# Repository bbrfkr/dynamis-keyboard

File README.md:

# dynamis
"dynamis" is the open-source 65% keyboard integrated with trackball.

## concept
- upgradable
    - This keyboard can be upgraded from sandwitch mounted case to gasket mounted case.
- input only with this 
    - This keyboard is integrated with 34mm trackball, so you need only this to input!
- compact and major
    - 65% layout that is compact and major have been adopted.
- rich layout options
    - split backspace, split left and right shift, split space and iso enter are supported.

## supported key layout

## how to build
### Collect Parts
1. Order semi-assembled pcb by following the [gerbers](https://github.com/bbrfkr/dynamis-keyboard/tree/main/gerbers), [bom](https://github.com/bbrfkr/dynamis-keyboard/blob/main/bom.csv) and [positions](https://github.com/bbrfkr/dynamis-keyboard/blob/main/dynamis-pos.csv) files.
1. Order fr4 plate by following the [plate gerbers](https://github.com/bbrfkr/dynamis-keyboard/tree/main/plate/gerbers).
1. Order the 3d print for trackball cup by the following [stl file](https://github.com/bbrfkr/dynamis-keyboard/blob/main/trackball-cup/trackball-cup.stl) (Here, FDM print should be selected).
1. Choose case options between [sandwitch](https://github.com/bbrfkr/dynamis-keyboard/tree/main/case/sandwitch) and [3d printed](https://github.com/bbrfkr/dynamis-keyboard/tree/main/case/3dp).
1. Collect parts by following the [pcba BOM.md](https://github.com/bbrfkr/dynamis-keyboard/blob/main/BOM.md) and the each BOM.md of selected case option.

### Assemble
1. Assemble semi-assembled pcb completely by following the [pcba build guide](https://github.com/bbrfkr/dynamis-keyboard/blob/main/BUILD.md)
1. Assemble case by following the each BUILD.md of selected case option.

## flash firmware
"dynamis" supports [qmk](https://github.com/qmk/qmk_firmware/tree/master/keyboards/bbrfkr/dynamis). Therefore, you can flash firmware by using [qmk toolbox](https://github.com/qmk/qmk_toolbox).

You can download the firmware for this keyboard from [here](https://github.com/bbrfkr/dynamis-keyboard/releases).

## remap keymap
"dynamis" supports [via](https://www.caniusevia.com/). Therefore, it is recommended that you remap keymap through via. You can download the via definition from [here](https://github.com/bbrfkr/dynamis-keyboard/releases). However, w.r.t. dynamis v2, `KC_F18` and `KC_F19` is hard-coded with `increase DPI` and `decrease DPI` features.

Moreover, "dynamis" is registered in [remap](https://remap-keys.app/catalog/stOy3bAlBUlsGzHCaDIQ). From this, you can remap keymap through web browser.

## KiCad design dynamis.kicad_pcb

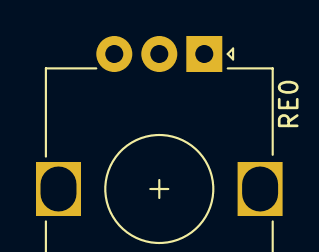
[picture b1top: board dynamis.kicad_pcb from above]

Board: 2 copper layers, 77 parts (0 on the bottom side), 13 nets, no tracks yet.

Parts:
RE0: RotaryEncoder; RotaryEncoder_Alps_EC12E_Vertical_H20mm
SW00_00, SW00_01, SW00_02, SW00_03, SW00_04, SW00_05, SW00_06, SW01_01, SW01_02, SW01_03, SW01_04, SW01_05, SW01_06, SW02_01, SW02_02, SW02_03, SW02_04, SW02_05, SW02_06, SW03_02, SW03_03, SW03_04, SW03_05, SW03_06, SW05_01, SW05_02, SW05_03, SW05_04, SW05_05, SW05_06, SW06_00, SW06_01, SW06_02, SW06_03, SW06_04, SW06_05, SW06_06, SW07_01, SW07_02, SW07_03, SW07_04, SW07_05, SW07_06, SW08_00, SW08_02, SW08_03, SW08_04, SW08_05, SW08_06, SW09_00, SW09_01, SW09_02, SW09_03, SW09_04: SW_Push; MXOnly-1U-Hotswap
SW01_00: SW_Push; MXOnly-1.5U-Hotswap
SW03_00, SW04_00, SW04_01, SW04_02, SW04_06, SW09_05, SW09_06: SW_Push; MXOnly-1.25U-Hotswap
SW04_03: SW_Push; MXOnly-2.25U-Hotswap-ReversedStabilizers
SW04_05: SW_Push; MXOnly-2.75U-Hotswap-ReversedStabilizers
SWBS_L00: SW_Push; MXOnly-2U-Hotswap
SWBS_S00: SW_Push; MXOnly-1U-Hotswap
SWCL_N00: SW_Push; MXOnly-1.75U-Hotswap
SWCL_S00: SW_Push; MXOnly-1U-Hotswap
SWET_AN00: SW_Push; MXOnly-1U-Hotswap
SWET_IS00: SW_Push; MXOnly-2U-Hotswap-ReversedStabilizers
SWLS_L01: SW_Push; MXOnly-2.25U-Hotswap
SWLS_S01: SW_Push; MXOnly-1U-Hotswap
SWRS_L01: SW_Push; MXOnly-2.75U-Hotswap
SWRS_S01: SW_Push; MXOnly-1.75U-Hotswap
SWSP_L04: SW_Push; MXOnly-6.25U-Hotswap
SWSP_S04: SW_Push; MXOnly-1.25U-Hotswap

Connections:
unnamed: SWCL_N00.2, SWCL_S00.2
unnamed: SWLS_L01.2, SWLS_S01.2
unnamed: SWSP_L04.2, SWSP_S04.2
unnamed: SWBS_L00.2, SWBS_S00.2
unnamed: SWET_AN00.2, SWET_IS00.2
unnamed: SWRS_L01.2, SWRS_S01.2
col00: SW00_00.1, SW01_00.1, SW03_00.1, SW04_00.1, SW06_00.1, SW08_00.1, SW09_00.1, SWBS_L00.1, SWBS_S00.1, SWCL_N00.1, SWCL_S00.1, SWET_AN00.1, SWET_IS00.1
col01: SW00_01.1, SW01_01.1, SW02_01.1, SW04_01.1, SW05_01.1, SW06_01.1, SW07_01.1, SW09_01.1, SWLS_L01.1, SWLS_S01.1, SWRS_L01.1, SWRS_S01.1
col02: SW00_02.1, SW01_02.1, SW02_02.1, SW03_02.1, SW04_02.1, SW05_02.1, SW06_02.1, SW07_02.1, SW08_02.1, SW09_02.1
col03: SW00_03.1, SW01_03.1, SW02_03.1, SW03_03.1, SW04_03.1, SW05_03.1, SW06_03.1, SW07_03.1, SW08_03.1, SW09_03.1
col04: SW00_04.1, SW01_04.1, SW02_04.1, SW03_04.1, SW05_04.1, SW06_04.1, SW07_04.1, SW08_04.1, SW09_04.1, SWSP_L04.1, SWSP_S04.1
col05: SW00_05.1, SW01_05.1, SW02_05.1, SW03_05.1, SW04_05.1, SW05_05.1, SW06_05.1, SW07_05.1, SW08_05.1, SW09_05.1
col06: SW00_06.1, SW01_06.1, SW02_06.1, SW03_06.1, SW04_06.1, SW05_06.1, SW06_06.1, SW07_06.1, SW08_06.1, SW09_06.1

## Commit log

2022-06-02 initial
2022-06-11 debug svg
2022-06-12 gasket mount case
2022-06-12 remove unneeded data
2022-06-12 mod bottom case for skrew hole
2022-06-19 mod name of 3dp gasket mount case dir
2022-06-19 mod .gitignore
2022-06-26 impl pcb
2022-06-27 add foam sheet graphics
2022-07-09 acrylic case
2022-07-09 add acrylic case model
2022-07-09 initial as features (#1)
    機能として完成した最初のコミット
2022-07-14 add logo
2022-07-14 move gerbers and add bom template
2022-07-14 update imgur link
2022-07-14 update imgur links
2022-07-14 mod readme
2022-07-14 mod typo
2022-07-14 mod capital letter
2022-07-14 mod bom
2022-07-15 mod boms of cases
2022-07-15 mod boms of cases and readme
2022-07-15 mod readmes
2022-07-15 apply license
2022-07-15 add build.md
2022-07-15 add each dynamis images
2022-07-15 mod to use images branch's images
2022-07-15 mod build guide
2022-07-15 add supported layout image
2022-07-15 add trailing dot
2022-07-15 add build guide and readme for trackball cup
2022-07-15 mod title
2022-07-15 mod stabilizer type
2022-07-15 mod build
2022-07-15 Add docs and logos (#2)
2022-07-15 fix miss link
2022-07-15 fix miss link (#3)
2022-07-16 add ja docs
2022-07-16 move master to main
2022-07-16 Docs ja (#4)
2022-07-16 mod miss link
2022-07-16 mod miss link (#5)
2022-07-16 mod ja -> jp
2022-07-16 mod ja -> jp (#6)
2022-07-16 mod miss link (#7)
2022-07-16 mod the thickness of gasket mount weight
2022-07-16 mod the thickness of gasket mount weight (#8)
2022-07-17 Revert "mod the thickness of gasket mount weight (#8)"
    This reverts commit 7079f59b7b411e1b7f8ee4e9c4865372847dab10.
2022-07-17 Revert "mod the thickness of gasket mount weight (#8)" (#9)
    This reverts commit 7079f59b7b411e1b7f8ee4e9c4865372847dab10.
2022-07-17 mod-bottom-case-stl
2022-07-17 mod-bottom-case-stl (#10)
2022-07-17 Revert "mod-bottom-case-stl (#10)"
    This reverts commit dcce82f15c9197485225979a70152f3f4f279621.
2022-07-17 Revert "mod-bottom-case-stl (#10)" (#11)
    This reverts commit dcce82f15c9197485225979a70152f3f4f279621.
2022-07-17 Revert "Revert "mod the thickness of gasket mount weight (#8)" (#9)"
    This reverts commit 5a923a44f460f610c11262448c813ee0f7480208.
2022-07-17 Revert "Revert "mod the thickness of gasket mount weight (#8)" (#9)" (#12)
    This reverts commit 5a923a44f460f610c11262448c813ee0f7480208.
2022-07-17 mod bom of 3dp
2022-07-17 mod readme of kit
2022-07-17 mod sandwitch build guide
2022-07-17 add images
2022-07-17 add dosc
2022-07-17 mod docs
2022-07-17 Mod manual (#13)
2022-07-17 mod images
2022-09-02 add firmware
2022-09-02 add github workflow
2022-09-02 mv workflow to workflows
2022-09-02 set env
2022-09-02 mod actions
2022-09-02 add release
2022-09-02 add condition to trigger test
2022-09-02 mod workflow and sub flows
2022-09-02 first firmware release (#15)
2022-09-12 mod firmware docs
2022-09-12 mod via image
2022-09-12 mod firmware docs (#17)
    mod firmware docs
2022-09-12 mod top readme
2022-09-12 mod top readme (#18)
2022-10-14 mod gasket thickness
2022-10-14 mod gasket thickness (#21)
2022-10-15 mod sandwitch bottom case
2022-10-15 mod sandwitch bottom case (#23)
2022-10-22 add fillet to 3dp case
2022-11-01 mod fillet
2023-04-27 add fillet to 3dp case (#25)
2023-04-27 change trackball support ball size
2023-04-27 remove acrylic case
2023-05-04 wip: switch layout
2023-05-04 wip: sk6812mini-e
2023-05-13 wip debug
2023-05-19 staging
2023-10-19 dynamis v2
2023-10-19 wip docs
2023-10-23 wip mod docs
2023-10-23 update images
2023-10-23 move images
2023-10-29 add v2 firmware
2023-10-29 add device version
2023-10-29 fix default layout
2023-10-29 Develop v2 (#27)
2023-10-29 fix release workflow to upload bbrfkr_dynamis_v2_via.hex
2023-10-29 fix release workflow to upload bbrfkr_dynamis_v2_via.hex (#28)
2023-11-03 feature: dynamical change cpi of trackball sensor
2023-11-03 fix document
